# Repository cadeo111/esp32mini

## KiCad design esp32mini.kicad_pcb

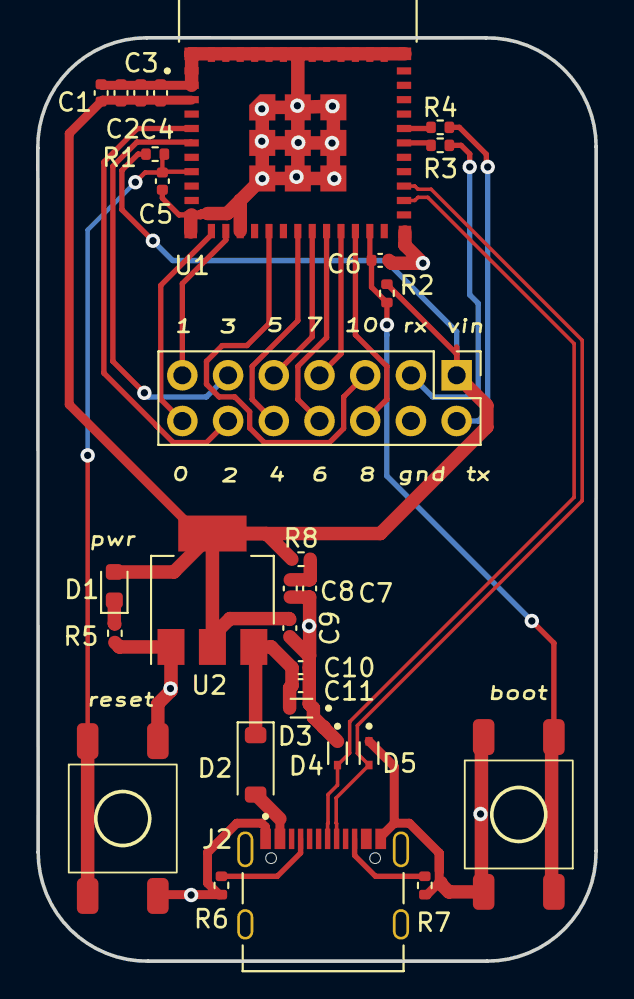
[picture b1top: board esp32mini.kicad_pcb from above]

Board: 2 copper layers, 31.0 x 51.3 mm, 30 parts (0 on the bottom side), 26 nets.

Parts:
C1, C7, C8, C11: 10uF; C_0402_1005Metric
C2, C3, C4, C5, C6, C9, C10: 100nF; C_0402_1005Metric
D1: pwr; LED_0603_1608Metric
D2: 1N5819HW-7-F; D_SOD-123
D3, D4, D5: LESD5D5.0CT1G; TVS_LESD5D5.0CT1G
J1: IO Header; PinHeader_2x07_P2.54mm_Vertical
J2: TYPE-C-31-M-12; HRO_TYPE-C-31-M-12
R1, R2, R5: 5.1k; R_0402_1005Metric
R3, R4: 470R; R_0402_1005Metric
R6, R7: 5k1; R_0402_1005Metric
R8: 10R; R_0402_1005Metric
SW1: reset; K2-6639SP-C4SC-04
SW2: boot; K2-6639SP-C4SC-04
U1: ESP32-C3-MINI-1-N4; XCVR_ESP32-C3-MINI-1-N4
U2: AMS1117-3.3; SOT-223-3_TabPin2

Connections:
+3.3V: C1.1, C2.1, C3.1, C4.1, C9.1, D1.2 (A), J1.1, R1.1, R2.1, R8.1, U1.3 (3V3), U2.2 (VO)
+5V: C10.1, C11.1, D2.1 (K), D3.2, U2.3 (VI)
/USB_D+: D5.2, J2.A6 (DP1), J2.B6 (DP2), U1.27 (IO19)
/USB_D-: D4.2, J2.A7 (DN1), J2.B7 (DN2), U1.26 (IO18)
/cc1: J2.A5 (CC1), R6.1
/cc2: J2.B5 (CC2), R7.1
/io0: J1.14, U1.12 (IO0)
/io1: J1.13, U1.13 (IO1)
/io2: J1.12, U1.5 (IO2)
/io3: J1.11, U1.6 (IO3)
/io4: J1.10, U1.18 (IO4)
/io5: J1.9, U1.19 (IO5)
/io6: J1.8, U1.20 (IO6)
/io7: J1.7, U1.21 (IO7)
/io8: J1.6, U1.22 (IO8)
/io9/boot: C6.2, R2.2, SW2.2 (B), U1.23 (IO9)
/io10: J1.5, U1.16 (IO10)
/io20/RX: J1.3, R3.1
/io21/TX: J1.2, R4.1
/mcu_en: C5.2, R1.2, SW1.2 (B), U1.8 (EN)
/rxd0_r_in: R3.2, U1.30 (RXD0)
/txd0_r_in: R4.2, U1.31 (TXD0)
/vo_r_out_c_in: C7.1, C8.1, R8.2
GND: C1.2, C2.2, C3.2, C4.2, C5.1, C6.1, C7.2, C8.2, C9.2, C10.2, C11.2, D3.1, D4.1, D5.1, J1.4, J2.A1_B12 (GND), J2.B1_A12 (GND), R5.2, R6.2, R7.2, SW1.1 (A), SW2.1 (A), U1.1 (GND), U1.2 (GND), U1.11 (GND), U1.14 (GND), U1.36 (GND), U1.37 (GND), U1.38 (GND), U1.39 (GND), U1.40 (GND), U1.41 (GND), U1.42 (GND), U1.43 (GND), U1.44 (GND), U1.45 (GND), U1.46 (GND), U1.47 (GND), U1.48 (GND), U1.49_1 (GND), U1.49_2 (GND), U1.49_3 (GND), U1.49_4 (GND), U1.49_5 (GND), U1.49_6 (GND), U1.49_7 (GND), U1.49_8 (GND), U1.49_9 (GND), U1.50 (GND), U1.51 (GND), U1.52 (GND), U1.53 (GND), U2.1 (GND)
unnamed: D1.1 (K), R5.1
VBUS: D2.2 (A), J2.A4_B9 (VBUS), J2.B4_A9 (VBUS)
